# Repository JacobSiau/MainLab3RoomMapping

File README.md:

# Lab3MainProject
ECE 3334 - Texas Tech University - Spring 2019 Main Project - Room Mapper 
***
Please see the wiki page of this repository for further project details. 
***

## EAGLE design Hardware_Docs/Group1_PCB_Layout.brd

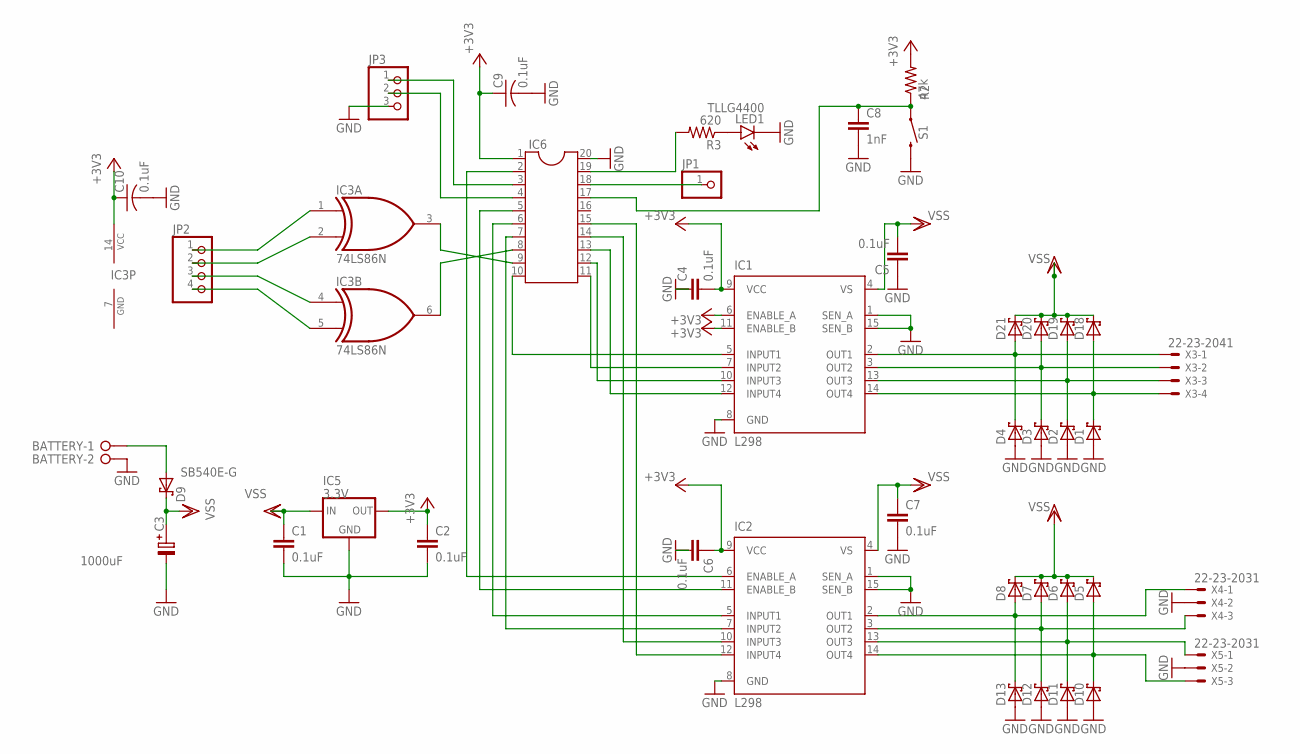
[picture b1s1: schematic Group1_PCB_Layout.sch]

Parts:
BATTERY: W237-02P; W237-132
C1, C2, C4, C5, C6, C7, C9, C10: 0.1uF; C1206
C3: 1000uF; E5,0-10
C8: 1nF; C1206
D1, D2, D3, D4, D5, D6, D7, D8, D10, D11, D12, D13, D18, D19, D20, D21: SCHOTTKY-DIODECB429-17; CB429-17
D9: SB540E-G; DO-201AD_UPRIGHT
IC1, IC2: L298; MULTIWATT-15
IC3: 74LS86N; DIL14
IC5: 3.3V; 78LXX
IC6: DIL20S; SOCKET-20
JP1: PINHD-1X1; 1X01
JP2: PINHD-1X4; 1X04
JP3: PINHD-1X3; 1X03
LED1: TLLG4400; LED3MM
R2: 47k; M1206
R3: 620; R1206
S1: MOMENTARY-SWITCH-SPST-PTH-6.0MM; TACTILE_SWITCH_PTH_6.0MM
X3: 22-23-2041
X4, X5: 22-23-2031

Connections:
+3V3: C2.1, C4.2, C6.1, C9.1, C10.1, IC1.6 (ENABLE_A), IC1.9 (VCC), IC1.11 (ENABLE_B), IC2.9 (VCC), IC3.14 (VCC), IC5.OUT, IC6.1, R2.2
EN_A1: IC2.6 (ENABLE_A), IC6.2
EN_B1: IC2.11 (ENABLE_B), IC6.5
GND: BATTERY.2, C1.2, C2.2, C3.-, C4.1, C5.1, C6.2, C7.2, C8.2, C9.2, C10.2, D1.A, D2.A, D3.A, D4.A, D10.A, D11.A, D12.A, D13.A, IC1.1 (SEN_A), IC1.8 (GND), IC1.15 (SEN_B), IC2.1 (SEN_A), IC2.8 (GND), IC2.15 (SEN_B), IC3.7 (GND), IC5.GND, IC6.20, JP3.3, LED1.K (C), S1.3 (2), X4.2, X5.2
unnamed: D4.C, D21.A, IC1.2 (OUT1), X3.1
unnamed: D3.C, D20.A, IC1.3 (OUT2), X3.2
unnamed: D2.C, D19.A, IC1.13 (OUT3), X3.3
unnamed: D1.C, D18.A, IC1.14 (OUT4), X3.4
unnamed: IC1.5 (INPUT1), IC6.10
unnamed: IC1.7 (INPUT2), IC6.11
unnamed: LED1.A, R3.1
unnamed: IC1.10 (INPUT3), IC6.12
unnamed: IC6.18, JP1.1
unnamed: IC6.19, R3.2
unnamed: D8.A, D13.C, IC2.2 (OUT1), X4.1
unnamed: D7.A, D12.C, IC2.3 (OUT2), X4.3
unnamed: D6.A, D11.C, IC2.13 (OUT3), X5.1
unnamed: D5.A, D10.C, IC2.14 (OUT4), X5.3
unnamed: IC1.12 (INPUT4), IC6.13
unnamed: IC2.7 (INPUT2), IC6.7
unnamed: IC2.5 (INPUT1), IC6.6
unnamed: IC2.10 (INPUT3), IC6.14
unnamed: BATTERY.1, D9.1 (A)
unnamed: IC3.3 (O), IC6.9
unnamed: IC3.1 (I0), JP2.1
unnamed: IC3.2 (I1), JP2.2
unnamed: IC6.4, JP3.2
unnamed: IC6.3, JP3.1
unnamed: IC3.4 (I0), JP2.3
unnamed: IC2.12 (INPUT4), IC6.15
unnamed: IC3.5 (I1), JP2.4
unnamed: IC3.6 (O), IC6.8
unnamed: C8.1, IC6.17, R2.1, S1.1
VSS: C1.1, C3.+, C5.2, C7.1, D5.C, D6.C, D7.C, D8.C, D9.2 (C), D18.C, D19.C, D20.C, D21.C, IC1.4 (VS), IC2.4 (VS), IC5.IN

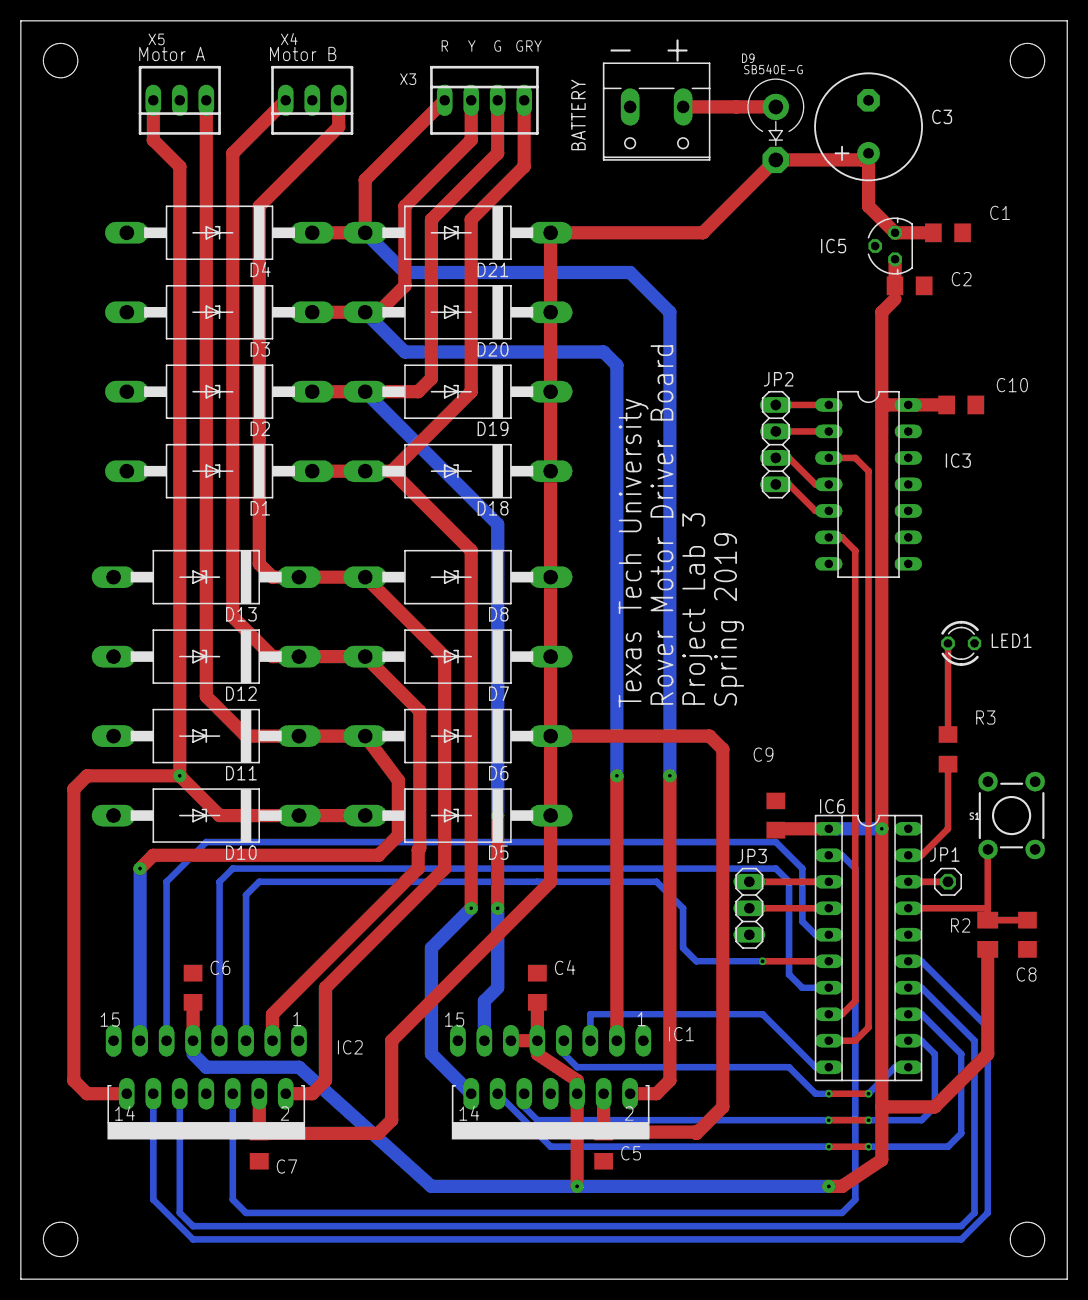
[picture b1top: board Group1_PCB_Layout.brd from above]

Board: 2 copper layers, 100.3 x 120.7 mm, 43 parts (0 on the bottom side), 34 nets.

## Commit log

2019-05-07 Create LICENSE
2019-05-07 Added Wiki
2019-05-07 Added Wiki Again
2019-05-07 Updated Wiki

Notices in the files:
parts and their libraries:
cap-pan40: Copyright (C) 2004, Bob Starr
SparkFun-Switches: Licensing: Creative Commons ShareAlike 4.0 International - https://creativecommons.org/licenses/by-sa/4.0
